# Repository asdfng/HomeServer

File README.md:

# HomeServer
 Small PCB Board for RPi CM4, running a home server

 This will be a small board used to power the RPi CM4. While I could just find something online I figure I'd learn a lot more if I tried making one myself.

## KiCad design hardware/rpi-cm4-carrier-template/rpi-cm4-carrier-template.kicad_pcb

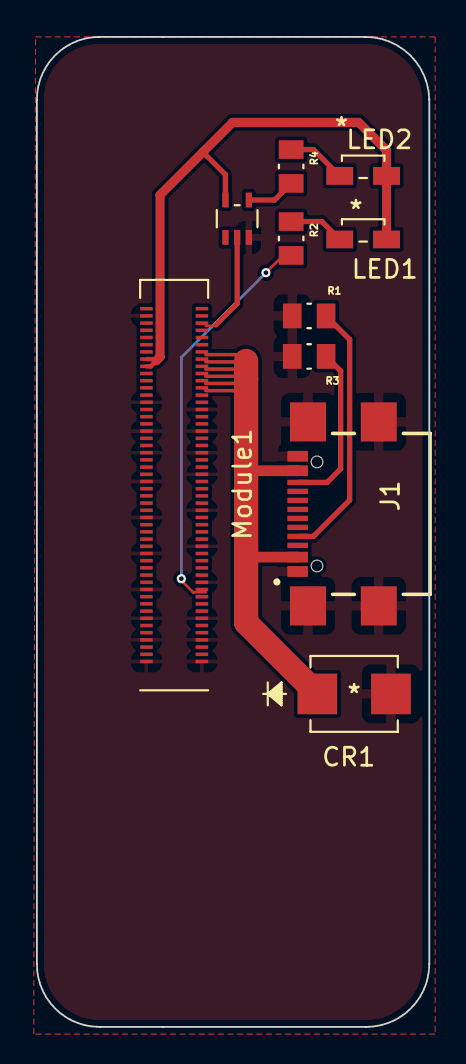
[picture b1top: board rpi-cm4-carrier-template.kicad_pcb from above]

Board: 2 copper layers, 21.8 x 55.0 mm, 10 parts (0 on the bottom side), 11 nets.

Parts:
CR1: SMBJ5.0A-TR
J1: USB4110-GF-A_REVB; GCT_USB4110-GF-A_REVB
LED1: Green LED; APA2106SUCK
LED2: Red LED; APA2106SUCK
Module1: ComputeModule4-CM4; MUnitA
R1, R2, R3, R4: ERJ-PB6B5101V; RESC2012X70N
U1: NLV17SZ07DFT2G

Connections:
+1.8V: Module1.88 (+1.8v_(Output)), Module1.90 (+1.8v_(Output))
+3.3V: LED1.2, LED2.2, Module1.84 (+3.3v_(Output)), Module1.86 (+3.3v_(Output)), U1.5 (VCC)
+5V: CR1.1, J1.A4/B9 (VBUS), J1.B4/A9 (VBUS), Module1.77 (+5v_(Input)), Module1.79 (+5v_(Input)), Module1.81 (+5v_(Input)), Module1.83 (+5v_(Input)), Module1.85 (+5v_(Input)), Module1.87 (+5v_(Input))
/CM4 GPIO/nLED_Activity: Module1.21 (PI_nLED_Activity), R2.2
/CM4 GPIO/nPWR_LED: Module1.95 (nPI_LED_PWR), U1.2 (INA)
GND: CR1.2, J1.A1/B12 (GND), J1.B1/A12 (GND), J1.S1 (GND), J1.S2 (GND), J1.S3 (GND), J1.S4 (GND), Module1.1 (GND), Module1.2 (GND), Module1.7 (GND), Module1.8 (GND), Module1.13 (GND), Module1.14 (GND), Module1.22 (GND), Module1.23 (GND), Module1.32 (GND), Module1.33 (GND), Module1.42 (GND), Module1.43 (GND), Module1.52 (GND), Module1.53 (GND), Module1.59 (GND), Module1.60 (GND), Module1.65 (GND), Module1.66 (GND), Module1.71 (GND), Module1.74 (GND), Module1.98 (GND), R1.2, R3.2, U1.3 (GND)
unnamed: J1.A5 (CC1), R1.1
unnamed: J1.B5 (CC2), R3.1
unnamed: LED1.1, R2.1
unnamed: LED2.1, R4.1
unnamed: R4.2, U1.4 (OUTY)

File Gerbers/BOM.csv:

"Id";"Designator";"Package";"Quantity";"Designation";"Supplier and ref";
1;"CR1";"SMBJ5.0A-TR";1;"SMBJ5.0A-TR";;;
2;"U1";"NLV17SZ07DFT2G";1;"NLV17SZ07DFT2G";;;
3;"R2,R4,R3,R1";"RESC2012X70N";4;"ERJ-PB6B5101V";;;
4;"LED1";"APA2106SUCK";1;"Green LED";;;
5;"J1";"GCT_USB4110-GF-A_REVB";1;"USB4110-GF-A_REVB";;;
6;"LED2";"APA2106SUCK";1;"Red LED";;;
7;"Module1";"MUnitA";1;"ComputeModule4-CM4";;;

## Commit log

2021-08-25 Update README.md
    First Commit
2021-08-26 Updated Schematic Layout
2021-08-27 Completed PCB Layout
2022-02-16 updated mezzanine connector footprint
2022-02-23 updated PCB layout

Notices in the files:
hardware/rpi-cm4-carrier-template/rpi-cm4-carrier-template.kicad_pcb:
creativecommons.org/licenses/by/4.0
License: CC BY 4.0
parts and their libraries:
Copyright 2021 Accelerated Designs. All rights reserved.
